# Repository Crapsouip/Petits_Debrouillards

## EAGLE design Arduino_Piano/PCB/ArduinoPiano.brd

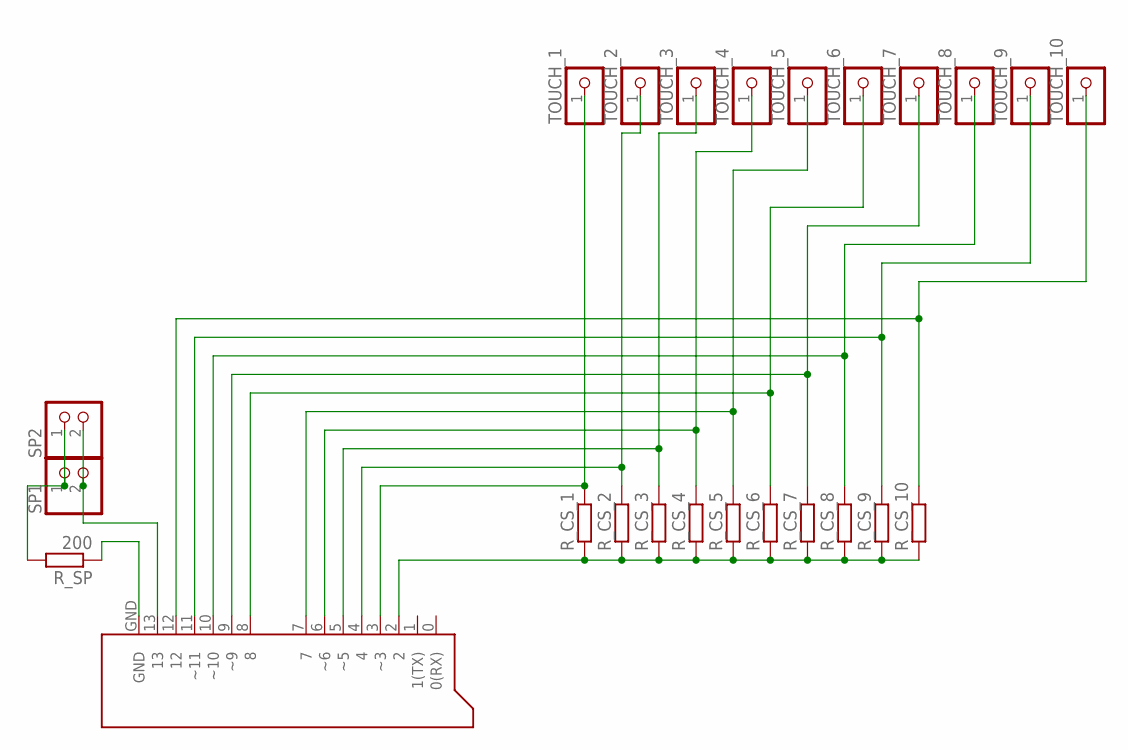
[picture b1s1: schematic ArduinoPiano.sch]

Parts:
PCB1: ARDUINO_UNO
R_CS_1, R_CS_2, R_CS_3, R_CS_4, R_CS_5, R_CS_6, R_CS_7, R_CS_8, R_CS_9, R_CS_10: R-EU_0204/7; 0204/7
R_SP: 200; 0204/7
SP1, SP2: PINHD-1X2; 1X02
TOUCH_1, TOUCH_2, TOUCH_3, TOUCH_4, TOUCH_5, TOUCH_6, TOUCH_7, TOUCH_8, TOUCH_9, TOUCH_10: PINHD-1X1; 1X01

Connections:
+SPEAKER: PCB1.13, SP1.2, SP2.2
CS_REC_1: PCB1.3 (~3), R_CS_1.2, TOUCH_1.1
CS_REC_2: PCB1.4, R_CS_2.2, TOUCH_2.1
CS_REC_3: PCB1.5 (~5), R_CS_3.2, TOUCH_3.1
CS_REC_4: PCB1.6 (~6), R_CS_4.2, TOUCH_4.1
CS_REC_5: PCB1.7, R_CS_5.2, TOUCH_5.1
CS_REC_6: PCB1.8, R_CS_6.2, TOUCH_6.1
CS_REC_7: PCB1.9 (~9), R_CS_7.2, TOUCH_7.1
CS_REC_8: PCB1.10 (~10), R_CS_8.2, TOUCH_8.1
CS_REC_9: PCB1.11 (~11), R_CS_9.2, TOUCH_9.1
CS_REC_10: PCB1.12, R_CS_10.2, TOUCH_10.1
CS_SEND: PCB1.2, R_CS_1.1, R_CS_2.1, R_CS_3.1, R_CS_4.1, R_CS_5.1, R_CS_6.1, R_CS_7.1, R_CS_8.1, R_CS_9.1, R_CS_10.1
GND_SPEAKER: PCB1.GND, R_SP.1
unnamed: R_SP.2, SP1.1, SP2.1

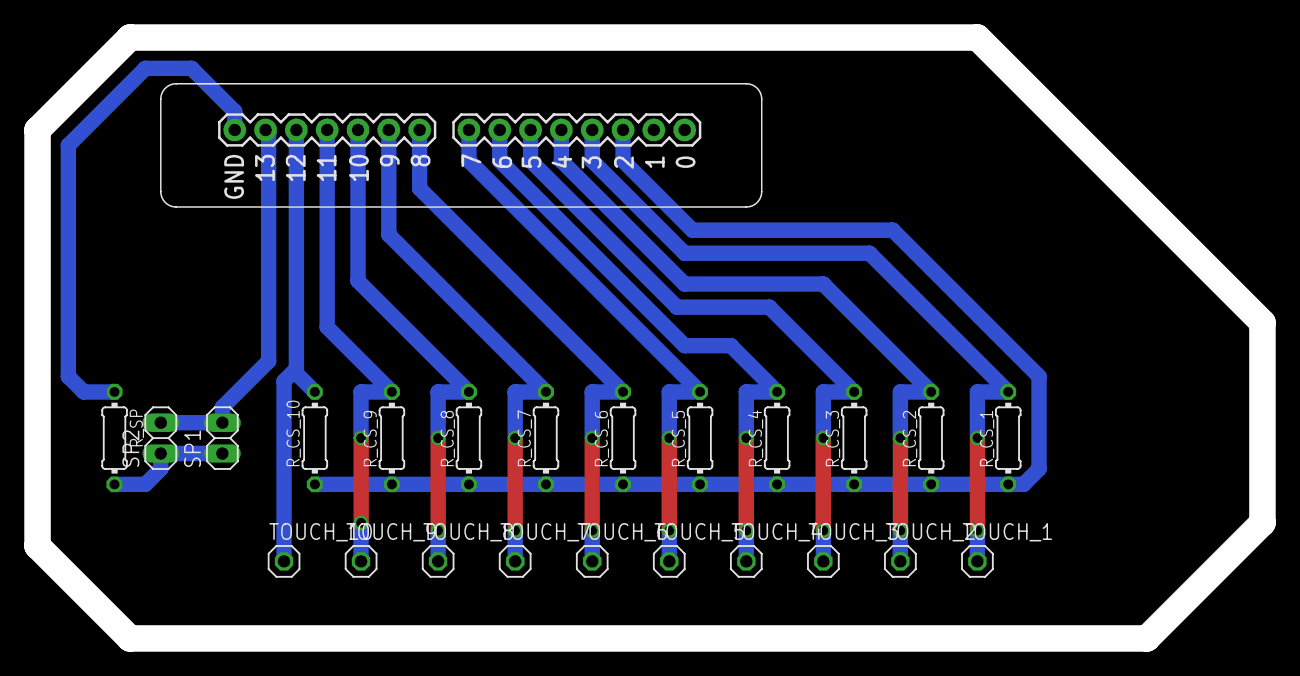
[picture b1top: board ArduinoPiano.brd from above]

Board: 2 copper layers, 101.0 x 49.5 mm, 24 parts (0 on the bottom side), 14 nets.

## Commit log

2015-11-18 :octocat: Added .gitattributes
2015-11-18 MyMagicStick : Intelligence V1.0
2015-11-18 MyMagicStick : Temperature Sensing Library V1.0
2015-11-18 MyMagicStick : Moisture Sensing Library V1.0
2015-11-18 MyMagicStick : Temperature & Humidity Sensing Library V1.0
2015-11-18 MyMagicStick : Luminosity Sensing Library V1.0
2015-11-18 MyMagicStick : Arduino Sketch
2015-11-18 MyMagicStick : Temperature Reading Arduino Example V1.0
2015-11-18 MyMagicStick : Moisture Reading Arduino Example V1.0
2015-11-18 MyMagicStick : Luminosity Reading Arduino Example V1.0
2015-11-18 MyMagicStick : Parcours d'animation - Exemple 1
2015-11-18 MyMagicStick : Parcours d'animation - Exemple 2
2015-11-18 MyMagicStick : Parcours d'animation - Exemple 3
2015-11-18 MyMagicStick : Parcours d'animation - Exemple 4
2015-11-18 MyMagicStick : Parcours d'animation - Resultat Exemple 1
2015-11-18 MyMagicStick : Parcours d'animation - Resultat Exemple 2
2015-11-18 MyMagicStick : Parcours d'animation - Resultat Exemple 3
2015-11-18 MyMagicStick : Parcours d'animation - Resultat Exemple 4
2015-11-18 MyMagicStick - Librairies, Exemples, Parcours d'animation
2015-11-18 Reset
2015-11-18 MyMagicStick : Release 1.0
2015-11-18 Piano Arduino : Release 1.0
2015-12-04 MyMagicStick - Schemas Fritzing Release 1.0
2015-12-04 MyMagicStick - Plans JPG Release 1.0
2015-12-04 MyMagicStick - Pieces STEP Release 1.0
2015-12-04 MyMagicStick - Modele 3D STEP Release 1.0
2015-12-04 MyMagicStick - Plans PDF Release 1.0
2015-12-04 MyMagicStick - PCB Release 1.0
2015-12-04 MyMagicStick - Schemas Fritzing Rlelease 1.0
2015-12-04 PianoArduino - Pieces STEP Release 1.0
